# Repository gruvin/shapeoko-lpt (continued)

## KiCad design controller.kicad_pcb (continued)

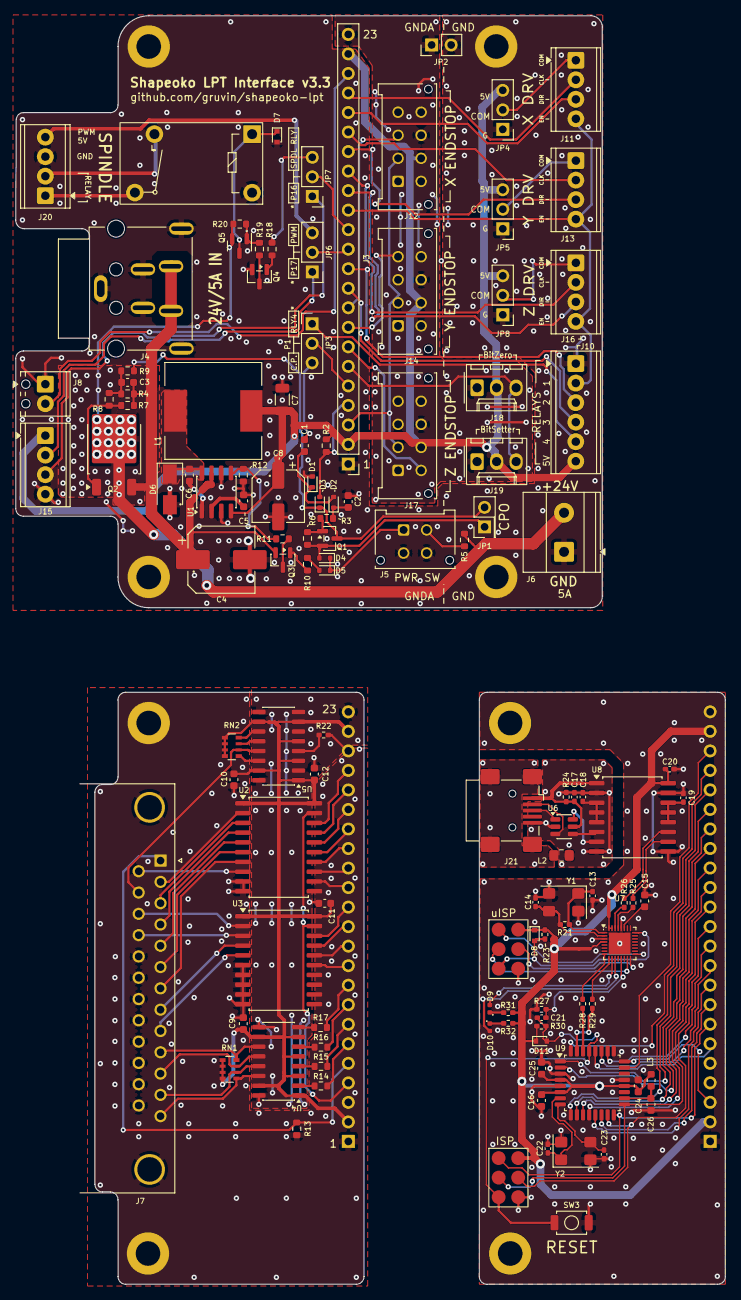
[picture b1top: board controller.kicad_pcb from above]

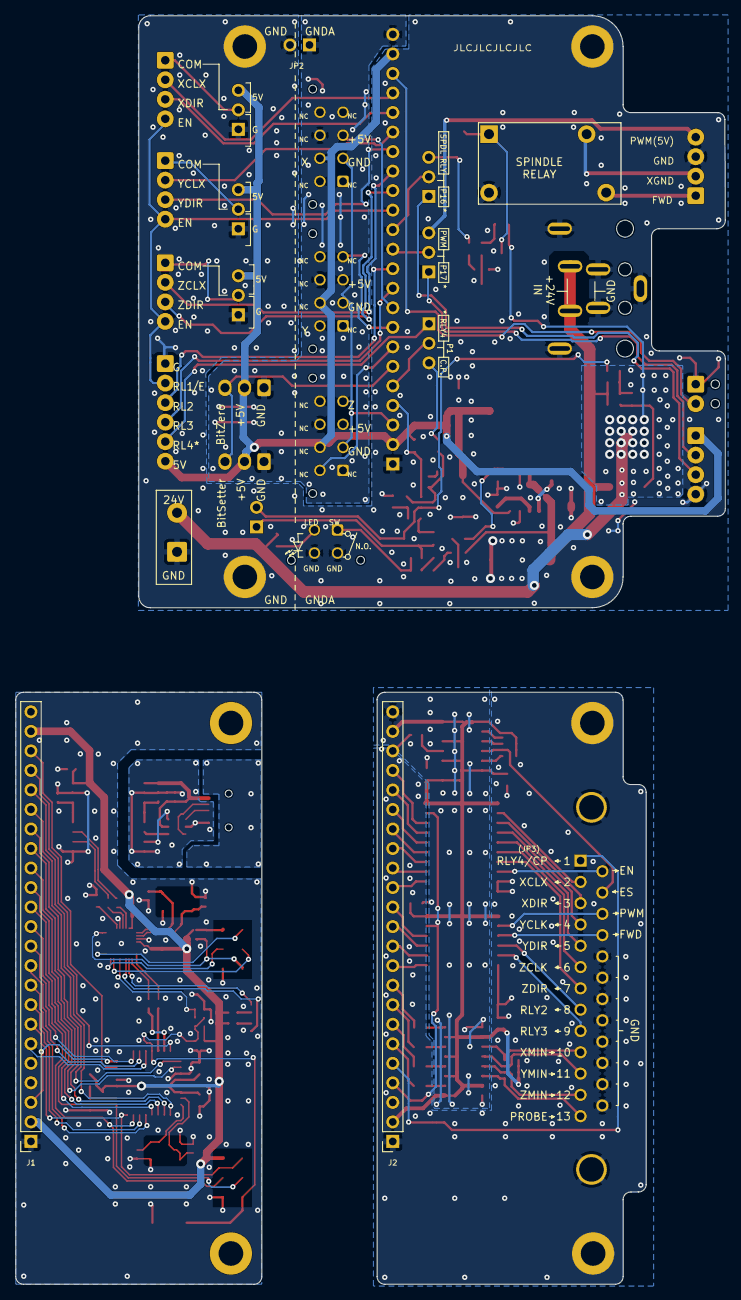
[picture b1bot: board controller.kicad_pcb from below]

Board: 2 copper layers, 92.3 x 165.0 mm, 137 parts (6 on the bottom side), 157 nets.

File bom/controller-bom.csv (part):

refs,qty,value,footprint,brand,mpn,supplier,sku,store,desc,status,stock,lead_days,moq,order_qty,unit,extended,currency,assembly,substituted,alternates,confidence,note
"C1,C5-C6,C9-C12",7,100n/50V,C_0603_1608Metric,MULTICOMP PRO,MC0603B104K500CT,element14,175912201,nz.element14.com,"SMD Multilayer Ceramic Capacitor, 0.1 µF, 50 V, 0603 [1608 Metric], ± 10%, X7R",STOCKED,1364666,161,10,10,0.023,0.23,NZD,SMD,,,high,
C2-C3,2,1u/50V,C_0603_1608Metric,MULTICOMP PRO,0603B105K500CT,element14,3764121,nz.element14.com,"SMD Multilayer Ceramic Capacitor, 1 µF, 50 V, 0603 [1608 Metric], ± 10%, X7R",STOCKED,47462,153,10,10,0.204,2.04,NZD,SMD,reviewed,,high,"reviewed: MULTICOMP consolidation: 1uF 50V 0603 X7R, replaces TDK C1608X5R1H105K080AB"
C4,1,100u/35V,CP_Elec_8x10.5_DOT,MULTICOMP PRO,MCVVT035M101FB3L,element14,2611382,nz.element14.com,"SMD Aluminium Electrolytic Capacitor, Radial Can - SMD, 100 µF, 35 V, 2000 hours @ 105°C, Polar",STOCKED,4803,145,1,1,0.837,0.837,NZD,SMD,reviewed,,high,"reviewed: MULTICOMP consolidation: 100uF 35V SMD electrolytic, 8.0mm dia x 10.5mm - matches the CP_Elec_8x10.5 footprint exactly"
C7,1,22u/16V,C_1206_3216Metric,MULTICOMP PRO,1206X226K160CT,element14,249715401,nz.element14.com,"SMD Multilayer Ceramic Capacitor, 22 µF, 16 V, 1206 [3216 Metric], ± 10%, X5R",STOCKED,10560,153,5,5,0.273,1.365,NZD,SMD,reviewed,,high,"reviewed: MULTICOMP consolidation (option b, chosen by Bryan): 22uF 16V 1206 X5R. MULTICOMP has no 22uF/25V 1206, so the schematic Value was changed to 22u/16V. Rail is the MAX5035 5V buck output, so 16V still gives 3.2x margin."
C8,1,68u/35V,CP_Elec_6.3x7.7_DOT,MULTICOMP PRO,MCVVT035M680EA6L,element14,2611393,nz.element14.com,"SMD Aluminium Electrolytic Capacitor, Radial Can - SMD, 68 µF, 35 V, 2000 hours @ 105°C, Polar",STOCKED,4294,145,1,1,0.443,0.443,NZD,SMD,reviewed,,high,"reviewed: MULTICOMP consolidation: 68uF 35V SMD electrolytic, 6.3mm dia x 7.7mm - matches the CP_Elec_6.3x7.7 footprint exactly"
"C13-C14,C22-C23",4,22p,C_0402_1005Metric_Pad0.74x0.62mm_HandSolder,MULTICOMP PRO,MC0402N220J500CT,element14,1758951,nz.element14.com,"SMD Multilayer Ceramic Capacitor, 22 pF, 50 V, 0402 [1005 Metric], ± 5%, C0G / NP0",STOCKED,53540,189,10,10,0.02,0.20,NZD,SMD,,,high,
C15,1,1u,C_0603_1608Metric,MULTICOMP PRO,0603B105K500CT,element14,3764121,nz.element14.com,"SMD Multilayer Ceramic Capacitor, 1 µF, 50 V, 0603 [1608 Metric], ± 10%, X7R",STOCKED,47462,153,10,10,0.204,2.04,NZD,SMD,reviewed,,high,reviewed: MULTICOMP consolidation: 1uF 50V 0603 X7R
"C16,C24-C26",4,100n,C_0603_1608Metric,MULTICOMP PRO,MC0603B104K500CT,element14,175912201,nz.element14.com,"SMD Multilayer Ceramic Capacitor, 0.1 µF, 50 V, 0603 [1608 Metric], ± 10%, X7R",STOCKED,1364666,161,10,10,0.023,0.23,NZD,SMD,reviewed,,high,"reviewed: MULTICOMP consolidation: 100nF 50V 0603 X7R, unified with C1 (same part, cheaper of the two listings)"
C17-C21,5,100n,C_0402_1005Metric_Pad0.74x0.62mm_HandSolder,MULTICOMP PRO,0402B104K500CT,element14,3764075,nz.element14.com,"SMD Multilayer Ceramic Capacitor, 0.1 µF, 50 V, 0402 [1005 Metric], ± 10%, X7R",STOCKED,59400,153,10,10,0.038,0.38,NZD,SMD,reviewed,,high,"reviewed: MULTICOMP consolidation: 100nF 50V 0402 X7R, replaces Murata GRM155R71H104KE14D"
D1-D5,5,SDM20U40-7,D_SOD-523,ONSEMI,NSR0340HT1G,element14,2317404,nz.element14.com,"Small Signal Schottky Diode, Single, 40 V, 250 mA, 590 mV, 1 A, 150 °C",STOCKED,32449,146,5,5,0.199,0.995,NZD,SMD,,,high,
D6,1,SS24A+,D_SMA_DOT,MULTICOMP PRO,SS24A,element14,2748189,nz.element14.com,"Schottky Rectifier, 40 V, 2 A, Single, DO-214AC (SMA), 2 Pins, 550 mV",STOCKED,12008,205,5,5,0.54,2.70,NZD,SMD,reviewed,,high,"reviewed: Value was 'SS24A+'; the trailing '+' is a lead-free suffix, the element14 MPN is SS24A. 40V 2A SMA matches the D_SMA footprint"
"D7-D8,D11",3,BAT54JFILM,D_SOD-523_DOT,STMICROELECTRONICS,BAT54KFILM,element14,2341638,nz.element14.com,"Small Signal Schottky Diode, 40 V, 300 mA, 900 mV, 1 A, 150 °C",STOCKED,7745,218,5,5,0.82,4.10,NZD,SMD,reviewed,,high,reviewed: BAT54KFILM is the SOD-523 version of the same BAT54 die (40V 300mA single Schottky). BAT54JFILM is SOD-323 - 1.9mm pad pitch vs the 1.4mm SOD-523 land pattern on the board - and is zero stock.
D9-D10,2,YELLOW,LED_0402_DOT,WURTH ELEKTRONIK,150040YS73240,element14,2900756,nz.element14.com,"LED, Yellow, SMD, 0402 [1005 Metric], 20 mA, 2 V, 590 nm",STOCKED,3092,84,5,5,0.58,2.90,NZD,SMD,reviewed,,high,reviewed: Value was just 'YELLOW'; footprint is LED_0402. Kingbright 150040YS73240 is a yellow 0402 LED
J1-J2,2,CONN_23W_SOCKET,PinSocket_1x23_P2.54mm_Vertical,Hong Cheng,HC-PM254-8.5H-1x23PZ,LCSC,C41376162,external,"23-way 2.54mm single-row socket, 8.5mm insulation height, 3mm tails, gold-flash contacts. 260 in stock, MOQ 5 = $1.15. Socket hangs below the interface board and receives the 15.75mm posts of J3 across the fixed 20.00mm standoff gap (socket body bottom at 11.5mm, pin tip at 15.75mm). Backup: HC-PM254-8.5H-1x24PZ = C41376163 (15714 stock, cut one position).",,,,,2,0.2297,0.4594,USD,THT,external,,external,"not from element14: 23-way 2.54mm single-row socket, 8.5mm insulation height, 3mm tails, gold-flash contacts. 260 in stock, MOQ 5 = $1.15. Socket hangs below the interface board and receives the 15.75mm posts of J3 across the fixed 20.00mm standoff gap (socket body bottom at 11.5mm, pin tip at 15.75mm). Backup: HC-PM254-8.5H-1x24PZ = C41376163 (15714 stock, cut one position)."
J3,1,CONN_23W_PIN,PinHeader_1x23_P2.54mm_Vertical,Samtec,TSW-123-17-T-S,Samtec,TSW-123-17-T-S,external,"23-way single-row 2.54mm THT header, .025in square posts, tin, lead style 17 = .620in (15.75mm) post above a 2.54mm plastic body, .830in (21.08mm) overall. The long post is what reaches the interface-board sockets across the fixed 20.00mm stack: measured requirement is 16.0 +/-0.25mm above the controller PCB, geometry says 15.75-16.25mm, and 15.75mm is the only stocked lead style in that window (-15 is 13.21mm, -18 is 18.29mm and would bottom out). In stock at Samtec, $1.516 ea. Exact-height alternative if 15.75mm proves marginal: MTSW-123-10-T-S-630 (.630in = 16.00mm post), build-to-order, no stock. Tail is 2.79mm = 1.19mm proud of a 1.6mm board.",,,,,1,1.516,1.516,USD,THT,external,,external,"not from element14: 23-way single-row 2.54mm THT header, .025in square posts, tin, lead style 17 = .620in (15.75mm) post above a 2.54mm plastic body, .830in (21.08mm) overall. The long post is what reaches the interface-board sockets across the fixed 20.00mm stack: measured requirement is 16.0 +/-0.25mm above the controller PCB, geometry says 15.75-16.25mm, and 15.75mm is the only stocked lead style in that window (-15 is 13.21mm, -18 is 18.29mm and would bottom out). In stock at Samtec, $1.516 ea. Exact-height alternative if 15.75mm proves marginal: MTSW-123-10-T-S-630 (.630in = 16.00mm post), build-to-order, no stock. Tail is 2.79mm = 1.19mm proud of a 1.6mm board."
J4,1,KYCON_KPJX-4S-S,KYCON_KPJX-4S-S,KYCON,KPJX-4S-S,element14,283985101,nz.element14.com,"High Power Connector, Through Hole RA, KPJX Series, Receptacle, 48 VDC, 7.5 A, PCB Mount",STOCKED,2471,99,1,1,2.40,2.40,NZD,THT,,,high,
J5,1,MicroFit_2x02,Molex_Micro-Fit_3.0_43045-0412_2x02_P3.00mm_Vertical,MOLEX,43045-0412,element14,101224701,nz.element14.com,"Pin Header, With Polarizing Peg, Wire-to-Board, 3 mm, 2 Rows, 4 Contacts, Through Hole Straight",STOCKED,25592,90,10,10,0.913,9.13,NZD,THT,,,high,
J6,1,24V/5A OUT,"TerminalBlock_Phoenix_MKDS-1,5-2-5.08_1x02_P5.08mm_Horizontal",PHOENIX CONTACT,1715721,element14,304152901,nz.element14.com,"Wire-To-Board Terminal Block, 5.08 mm, 2 Ways, 26 AWG, 14 AWG, 2.5 mm², Screw",STOCKED,7399,36,1,1,1.40,1.40,NZD,THT,,,high,
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
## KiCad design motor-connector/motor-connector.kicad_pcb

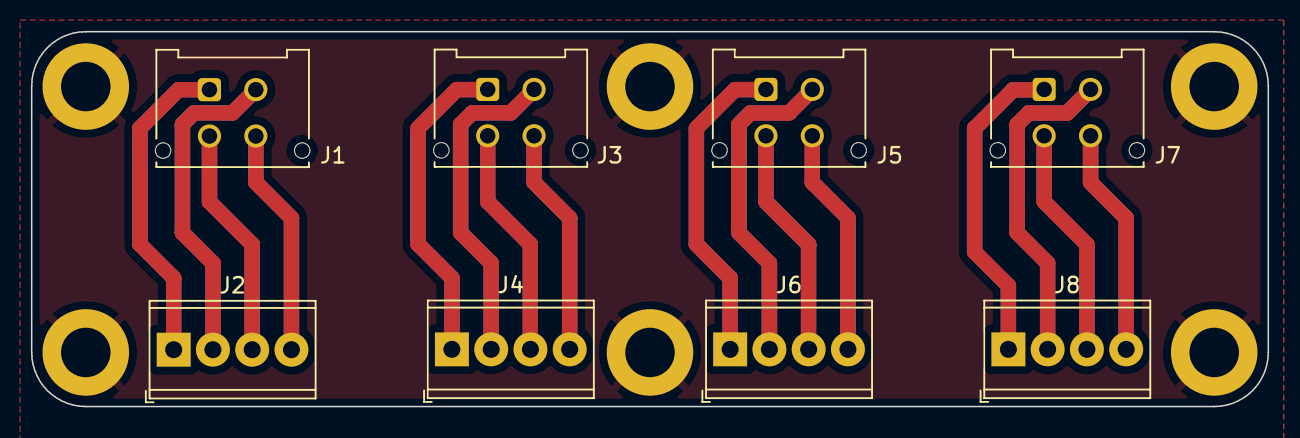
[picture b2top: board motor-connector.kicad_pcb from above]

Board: 2 copper layers, 80.0 x 24.2 mm, 14 parts (0 on the bottom side), 17 nets.

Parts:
H1, H2, H3, H4, H5, H6: MountingHole_Pad; MountingHole_3.2mm_M3_DIN965_Pad
J1, J3, J5, J7: Conn_02x02_Top_Bottom; Molex_Micro-Fit_3.0_43045-0412_2x02_P3.00mm_Vertical
J2, J4, J6, J8: Conn_01x04; TerminalBlock_Phoenix_MPT-0,5-4-2.54_1x04_P2.54mm_Horizontal

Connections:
GND: H1.1, H2.1, H3.1, H4.1, H5.1, H6.1
unnamed: J1.1, J2.1
unnamed: J1.2, J2.2
unnamed: J1.3, J2.3
unnamed: J1.4, J2.4
unnamed: J3.1, J4.1
unnamed: J3.2, J4.2
unnamed: J3.3, J4.3
unnamed: J3.4, J4.4
unnamed: J5.1, J6.1
unnamed: J5.2, J6.2
unnamed: J5.3, J6.3
unnamed: J5.4, J6.4
unnamed: J7.1, J8.1
unnamed: J7.2, J8.2
unnamed: J7.3, J8.3
unnamed: J7.4, J8.4

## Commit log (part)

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2022-05-14 Add vanity images
2022-05-14 fix filename
2022-05-14 Much to do about OCD power distribution. (Removed all loop 'antennas' and balanced transmission lines..)
2022-05-14 Some more decoupling caps and routing optimizations.
2022-05-15 Lots of changes and errors fixed. Updated vanity images.
2022-05-15 Probe connectors wired wrong. Improved 5V buck reg layout.
2022-05-16 Added LEDs (more coming). Changes to charge pump and related power switching.
2022-05-16 Forgot R1 and more NT fun.
2022-05-17 Resistor networks changed to 0603 'cause JLCPCB has those as 'basic parts' & aunch of tweaks. (WIP)
2022-05-17 Silk screen work.
2022-05-17 temp
2022-05-17 Scary file corruption turns out to be just bugs in eschema.
2022-05-17 Removed 'Element14' field from all sch/pcb components
2022-05-18 Reworked PSU control scheme (schematic only.)
2022-05-18 sync other PC
2022-05-18 add missing module
2022-05-18 add empty(ish) folder as originally intended
2022-05-18 Change share/_footprints to share/module with new alias '-Project'
2022-05-18 Much to do about power
2022-05-19 Routed power switching changes.
2022-05-19 More power supply and 5A ground return routing optimization.
2022-05-19 Tweaks
2022-05-20 Tweaks and JLCPCB LCSC field name changes.
2022-05-20 Added 100n extra decoupling cap to PWM 12V reg.
2022-05-20 Added modules
2022-05-20 All available JLCPCB Part codes loaded.
2022-05-20 I'm soooo done with this board! :/
2022-05-21 Some fixes .... and ... a MAJOR fuck up on the power connector, after the board went into production already.
2022-05-21 Corrected unbelievably DUMB ballsup on input power connector.
2022-05-21 WIP tk XCIII
2022-05-22 More OCD hours really. I need to stop. It's getting stupid. :P
2022-05-22 DRC checks. Tagging as V1.0 'actual'
2022-05-22 Prepping JLCPCB order for v1.1 assembled boards.
2022-05-22 JLCPCB Order Placed.
2022-05-22 JLCPCB Order Placed for JLCPCB_V1.1_FROZEN/.
2022-05-23 Lost the top layer ground plane. Got sick of being in Via Hell.
2022-05-24 VERSION 2.0RC1
2022-05-24 Edit README and add new 24V relay sch module/
2022-05-24 More OCD'n
2022-05-24 Unfinished 5V buck routing optimization.
2022-05-25 V2.0_RC2
2022-05-25 Tweaks & recorded custom 3D Viewer colors.
2022-05-25 Couple tweaks and updated vanity images.
2022-05-26 LED city
2022-05-27 Fixed stupid error with LED circuit. (LED are lights, yes but they only turn on when current is going a certain direction. Duh. LOL)
2022-05-28 Mostly groundplane declutter and loop removal.
2022-05-28 More ground plane clearance/optimization.
2022-05-29 Moving charge pump 15KHz input closer to source,
2022-05-29 V2.0RC2
2022-05-31 Tweaked .gitignore
2022-05-31 Fixed opto-isolator wrong part and added jumper to isolate A/DGNDs.
2022-05-31 Chnaged opto-couplers to 3-ch versions. Cheaper and less waste[.|?]
2022-06-01 Fixed yesterday's fix. Changed relay layout to allow 3A max terminal current, actually. Also changed VFD 0-10V PCB Farraday shield to reference VFD AGND instead of local GND.
2022-06-01 Tidied up F.Fab and some silk screen. Added back 2 missing tooling holes.
2022-06-01 Part supply references wip.
2022-06-01 WIP: Changing to terminal blocks for stepper, relay and VFD ports.
2022-06-01 Completed change to screw terminal blocks. (P16/17 remains JST.)
2022-06-01 Changed name to Shapeoko LPT Interface v2.0
2022-06-01 'Fixed' CAM/Grid origins.
2022-06-02 Silkscreen errors
2022-06-02 Completed element14 part codes
2022-06-03 Change and reposition JP16/17 connector to screw terminal.
2022-06-04 Moved LF1 to location afforded by new relay position.
2022-06-04 Minor silk tweaks. Update vanity images.
2022-06-04 Moved LPT left to protrude just over the PCB edge. Moved power connector inward to increase 24V/GND clearance.
2022-06-06 JLCPCB_V2.0_FROZEN
2022-06-15 V2.1 after errors found on physical V2.0 boards. sigh
2022-06-16 'Final' tidy-up before trying physical boards production, yet again. Frankly, this is getting ridiculous. Never made so many mistakes on such a simple board. Getting too old? (51)
2022-07-08 Correct Q1 pin muddle.
2022-07-08 Correct Q5 pin muddle.
2022-07-08 Charge pump signal re-routed.
    Funny how the CP signal can't get through if /CE not asserted but /CE can only be asserted if the charge pump signal present. Oops. :/
2022-07-08 Added BC847 BC857 datasheets locally for convenience.
2022-07-08 Corrected J2 pinout
2022-07-09 Fixed all three endstop pinout errors. :/
2022-07-09 JLCPCB_V3.0
2022-07-09 Add production files for JLCPCB_V3.0_FROZEN
2022-07-09 Added fab plot to production files. Bumped PCB version to 3.1.
2022-07-16 Added 1GW and 3FW part marking to values of the bp transistors.
2022-07-20 Added motor / driver interface PCBs
2023-02-13 Two board version taking shape
2023-02-14 checkpoint
2023-02-15 v4 MILESTONE
2023-02-24 MILESTONE: Shrinkage Tk II
2023-02-24 MILESTONE: Shrinkage Tk II -- Added two more mouonting holes
2023-02-24 clean up
2023-02-28 MILSTONE: Production Candidate PC1
2023-03-01 GRBL interface board work underway
2023-04-12 Post build PWM hacks (better(ish))
2023-07-05 moved some connectors further "out"
2023-07-06 Optical isolator input current (10mA not 3mA) and wiring error fixed.
2023-07-07 Multiple flaws resolved
2023-07-09 Oh ... just a few more fuckups fixed
2023-07-11 v3.2 pre-production clean-up
2023-07-12 more clean-up
2023-07-12 commit to v3.2 production
2023-08-05 meta
